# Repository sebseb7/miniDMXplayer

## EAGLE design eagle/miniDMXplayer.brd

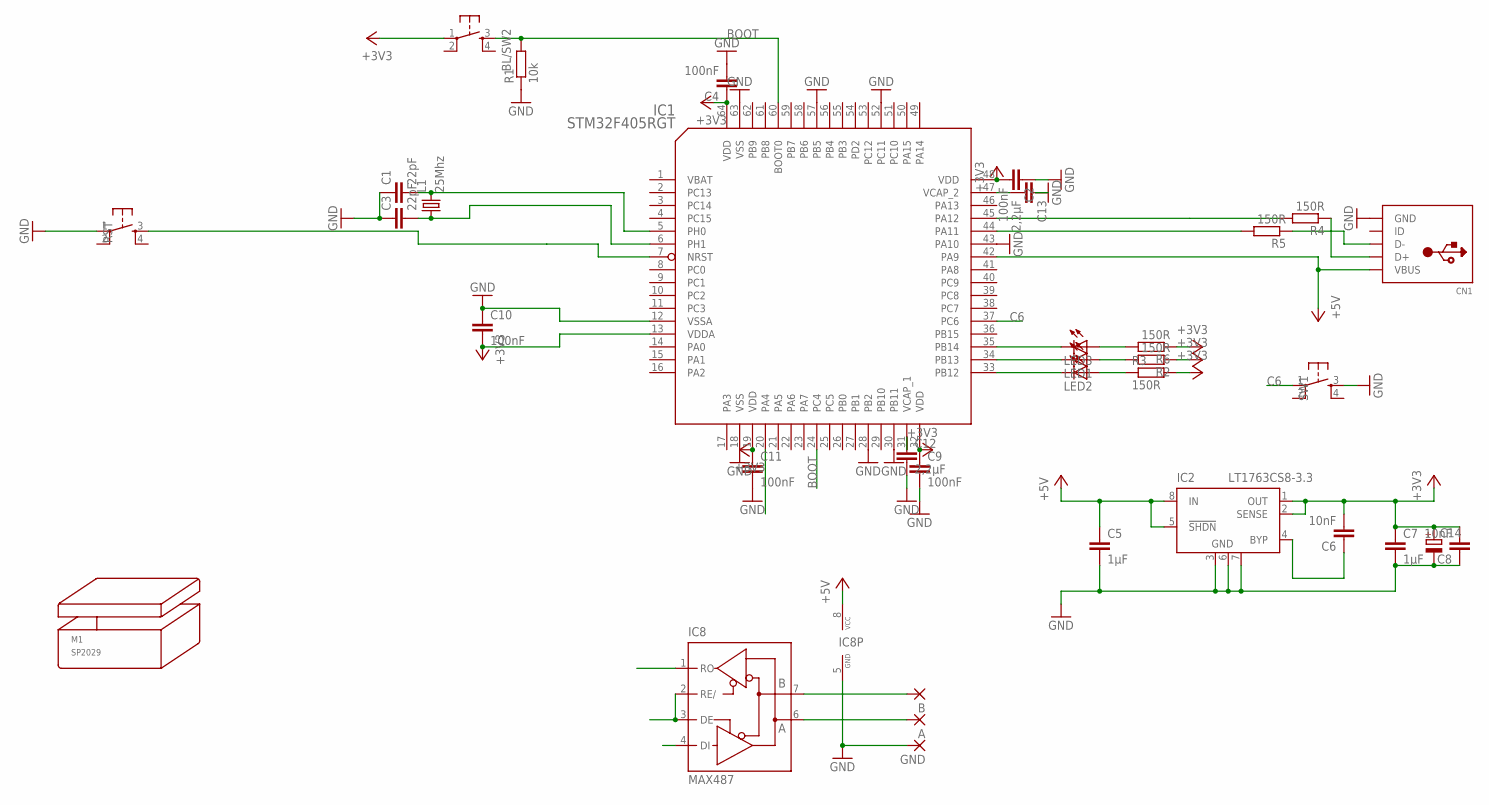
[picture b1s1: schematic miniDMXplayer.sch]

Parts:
A: SMD5; SMD2,54-5,08
B: SMD5; SMD2,54-5,08
BL/SW2: DTSM-6
C1, C3: 22pF; C0402
C2, C4, C9, C10, C11: 100nF; C0402
C5, C7: 1µF; 0805
C6, C8: 10nF; C0402
C12, C13: 2,2µF; 0805
C14: CPOL-EUSMCA; SMC_A
CN1: USBMINIB; USB-MINIB
GND: SMD5; SMD2,54-5,08
IC1: STM32F405RGT; LQFP64
IC2: LT1763CS8-3.3; SOIC8
IC8: MAX487; SO08
L1: 25Mhz; X22
LED1, LED2, LED3: LED0603; LED-0603
M1: SP2029
R1: 10k; R0402
R2, R3, R4, R5, R6: 150R; R0402
RST: DTSM-6
SW1: DTSM-6

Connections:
+3V3: BL/SW2.1, C2.2, C4.1, C6.2, C7.1, C8.2, C9.1, C10.2, C11.1, C14.+, IC1.13 (VDDA), IC1.19 (VDD), IC1.32 (VDD), IC1.48 (VDD), IC1.64 (VDD), IC2.1 (OUT), IC2.2 (SENSE), R2.1, R3.2, R6.1
+5V: C5.1, CN1.VBUS, IC1.42 (PA9), IC2.5 (!SHDN), IC2.8 (IN), IC8.8 (VCC)
A4: IC1.20 (PA4)
BOOT: BL/SW2.3, IC1.24 (PC4), IC1.60 (BOOT0), R1.2
C6: IC1.37 (PC6), SW1.1
GND: C1.1, C2.1, C3.1, C4.2, C5.2, C7.2, C8.1, C9.2, C10.1, C11.2, C12.2, C13.1, C14.-, CN1.GND, GND.1, IC1.12 (VSSA), IC1.18 (VSS), IC1.28 (PB2), IC1.30 (PB11), IC1.43 (PA10), IC1.52 (PC11), IC1.57 (PB5), IC1.63 (VSS), IC2.3 (GND), IC2.6 (GND), IC2.7 (GND), IC8.5 (GND), R1.1, RST.1, SW1.3
unnamed: IC1.35 (PB14), LED3.C
unnamed: IC8.2 (RE/), IC8.3 (DE)
unnamed: C3.2, IC1.6 (PH1), L1.1
unnamed: C1.2, IC1.5 (PH0), L1.3 (2)
unnamed: IC1.7 (NRST), RST.3
unnamed: LED3.A, R6.2
unnamed: B.1, IC8.7 (B)
unnamed: IC1.44 (PA11), R5.2
unnamed: A.1, IC8.6 (A)
unnamed: C12.1, IC1.31 (VCAP_1)
unnamed: C6.1, IC2.4 (BYP)
unnamed: C13.2, IC1.47 (VCAP_2)
unnamed: IC1.33 (PB12), LED2.C
unnamed: LED1.A, R2.2
unnamed: LED2.A, R3.1
unnamed: IC1.34 (PB13), LED1.C
unnamed: IC1.45 (PA12), R4.2
unnamed: CN1.D+, R4.1
unnamed: CN1.D-, R5.1
VBAT: IC1.1 (VBAT)

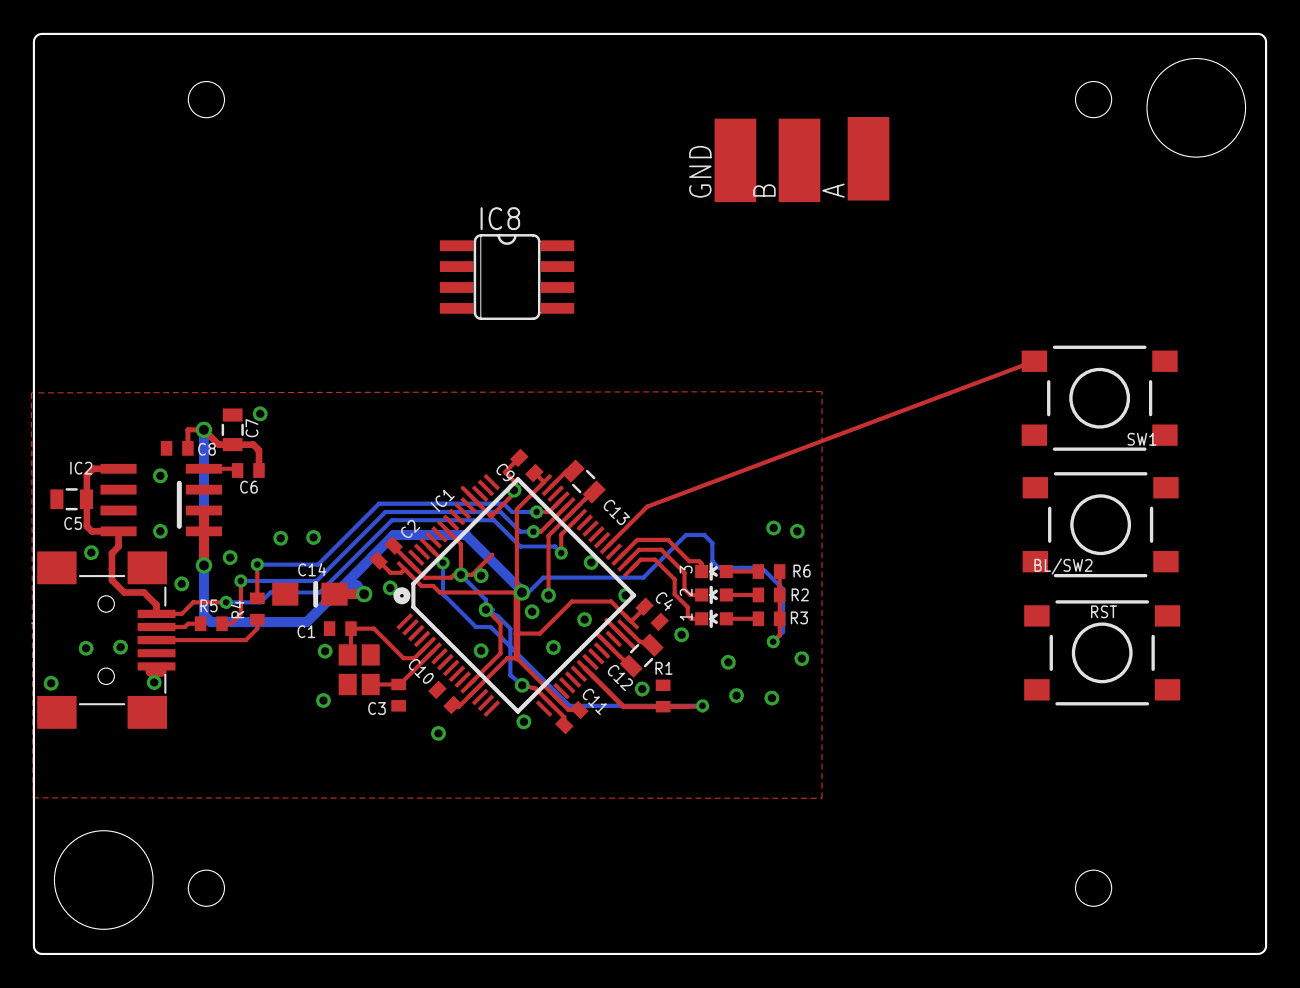
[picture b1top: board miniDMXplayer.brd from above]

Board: 2 copper layers, 75.0 x 56.0 mm, 35 parts (0 on the bottom side), 24 nets.

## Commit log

2013-08-03 initial
2013-08-03 ignore simulator binaries
2013-08-03 first version
2013-08-03 working firmware
2013-08-03 st-flash
2013-09-11 various updates
2013-09-11 new animations
2013-09-11 serial output for dmx adapter

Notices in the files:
parts and their libraries:
SparkFun-LED: Licensing: CC v3.0 Share-Alike You are welcome to use this library for commercial purposes.
